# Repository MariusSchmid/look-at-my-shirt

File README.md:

# look-at-my-shirt
T-Shirt for nerds making cool LED effects

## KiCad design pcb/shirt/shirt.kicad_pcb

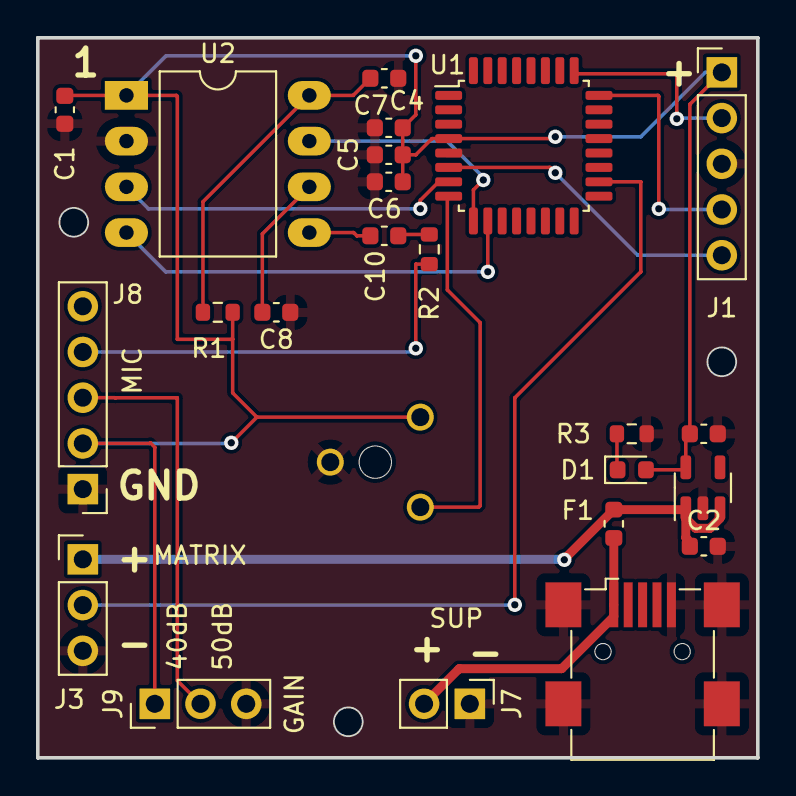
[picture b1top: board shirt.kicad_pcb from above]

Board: 2 copper layers, 40.0 x 40.0 mm, 24 parts (1 on the bottom side), 19 nets.

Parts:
C1, C2, C3, C5, C6, C8: 100nF; C_0603_1608Metric
C4: 4.7µF; C_0603_1608Metric
C7: 33 pF; C_0603_1608Metric
C10: 10nF; C_0603_1608Metric
D1: LED; LED_0603_1608Metric
F1: Fuse; Fuse_0603_1608Metric
J1: SWD; PinHeader_1x05_P2.54mm_Vertical
J2: USB_B_Mini; USB_Mini-B_Wuerth_65100516121_Horizontal
J3: LED_MATRIX; PinHeader_1x03_P2.54mm_Vertical
J7: Battery; PinHeader_1x02_P2.54mm_Vertical
J8: MIC; PinHeader_1x05_P2.54mm_Vertical
J9: GAIN; PinHeader_1x03_P2.54mm_Vertical
R1: 200k; R_0603_1608Metric
R2, R3: 22k; R_0603_1608Metric
U1: STM32G070KBTx; LQFP-32_7x7mm_P0.8mm
U2: DIP-8_W10.16mm_LongPads
U3: TCR2LF33; SOT-23-5
VR1: 601010

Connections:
+3.3V: C1.1, C3.1, C4.1, C5.1, C6.1, D1.2 (A), J1.1, J8.2, J9.1, R1.2, U1.4 (VDD), U2.1 (VDDA), U3.5 (OUT), VR1.1 (CCW)
+BATT: C2.1, F1.2, J3.1, U3.1 (IN), U3.3 (EN)
AUDIO_OUT: J8.4, R2.1
GND: C1.2, C2.2, C3.2, C4.2, C5.2, C6.2, C7.2, C8.2, J1.3, J2.5 (GND), J2.6 (Shield), J3.3, J7.1, J8.1, J9.3, R3.1, U1.5 (VSS), U2.2 (VSSA), U3.2 (GND), VR1.3 (CW)
LED_MATRIX_DIN: J3.2, U1.18 (PA8)
MSGEQ7_OUT: U1.7 (PA0), U2.3 (OUT)
MSGEQ7_RESET: U1.9 (PA2), U2.7 (RESET)
MSGEQ7_STROBE: U1.10 (PA3), U2.4 (STROBE)
NRST: J1.5, U1.6 (NRST)
unnamed: C10.2, R2.2
unnamed: D1.1 (K), R3.2
unnamed: J8.3, J9.2
unnamed: C7.1, R1.1, U2.8 (CKIN)
unnamed: C8.1, U2.6 (GND)
unnamed: C10.1, U2.5 (IN)
POTI_WIPER: U1.8 (PA1), VR1.2 (WIPER)
SWCLK: J1.2, U1.25 (PA14)
SWDIO: J1.4, U1.24 (PA13)
VBUS: F1.1, J2.1 (VBUS), J7.2

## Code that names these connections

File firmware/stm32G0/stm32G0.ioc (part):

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Mcu.Name=STM32G070KBTx
Mcu.Package=LQFP32
Mcu.UserName=STM32G070KBTx
PA0.GPIOParameters=GPIO_Label
PA0.GPIO_Label=MSGEQ7_OUT
PA0.Mode=IN0
PA0.Signal=ADC1_IN0
PA1.Mode=IN1
PA1.Signal=ADC1_IN1
PA2.GPIOParameters=GPIO_Label
PA2.GPIO_Label=MSGEQ7_RESET
PA2.Signal=GPIO_Input
PA3.GPIOParameters=GPIO_Label
PA3.GPIO_Label=MSGEQ7_STRUBE
PA3.Signal=GPIO_Input
PA8.Signal=S_TIM1_CH1
RCC.HSE_VALUE=8000000
RCC.SYSCLKFreq_VALUE=16000000
board=custom

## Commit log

2023-06-23 single led with 16 bit is working
2023-06-23 single led with 8bit array is working
2023-06-23 set led in matrix is working
2023-06-23 dvd animation working
2023-06-23 fixed color bug and frq is working
2023-06-24 frq is working with mic
2023-06-25 moved firmware to folder
2023-06-25 added pcb project
